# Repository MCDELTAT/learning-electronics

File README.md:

# Learning Electronics
## Author: Aaron Chamberlain

This repository holds simple circuit boards that are great for learning about electronics. Simply navigate to the individual folders for each project. In them, you will find the EAGLE board, schematic, and project files. In some cases there will be two versions, one to be milled on a CNC (I use the Bantam Tools CNC Machine to test these) and another to be manufactured by a service like OSHPARK. Both versions cant be sent to a manufacturer, but the CNC versions are not optimal because I often leave out vias, which are difficult to make on a milled board.

## Projects:
[Transistor Logic][logic]: This circuit is a simple implementation of the 4 basic logic gates, AND, OR, NOR, and NAND.

[logic]: ./transistor_logic/

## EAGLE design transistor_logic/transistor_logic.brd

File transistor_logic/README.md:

# Transistor Logic
This circuit is a simple implementation of the 4 basic logic gates, AND, OR, NOR, and NAND.

At this time, the circuit only has a version designed for a CNC machine. I will consider making a different version for fabrication with good silkscreens.

Bill of Materials (The Stuff You Need to Make This):

I recommend using Digikey or Mouser to find these products, I will try to provide part-numbers for them when possible.

* 1 9V Battery or Power Supply
* 1 8-Pin DIP Switch
* 8 3904 NPN Transistors
* 8 10K 1/2W Resistors
* 4 4.7K 1/2W Resistors
* 4 120R 1/2W Resistors
* 4 5mm LEDs of your choice

Note that it it recommended to change the resistor value of the 120R resistor if you change the LED color. I chose 120R because it's roughly middle of the road and what I needed for 4 green LEDs.

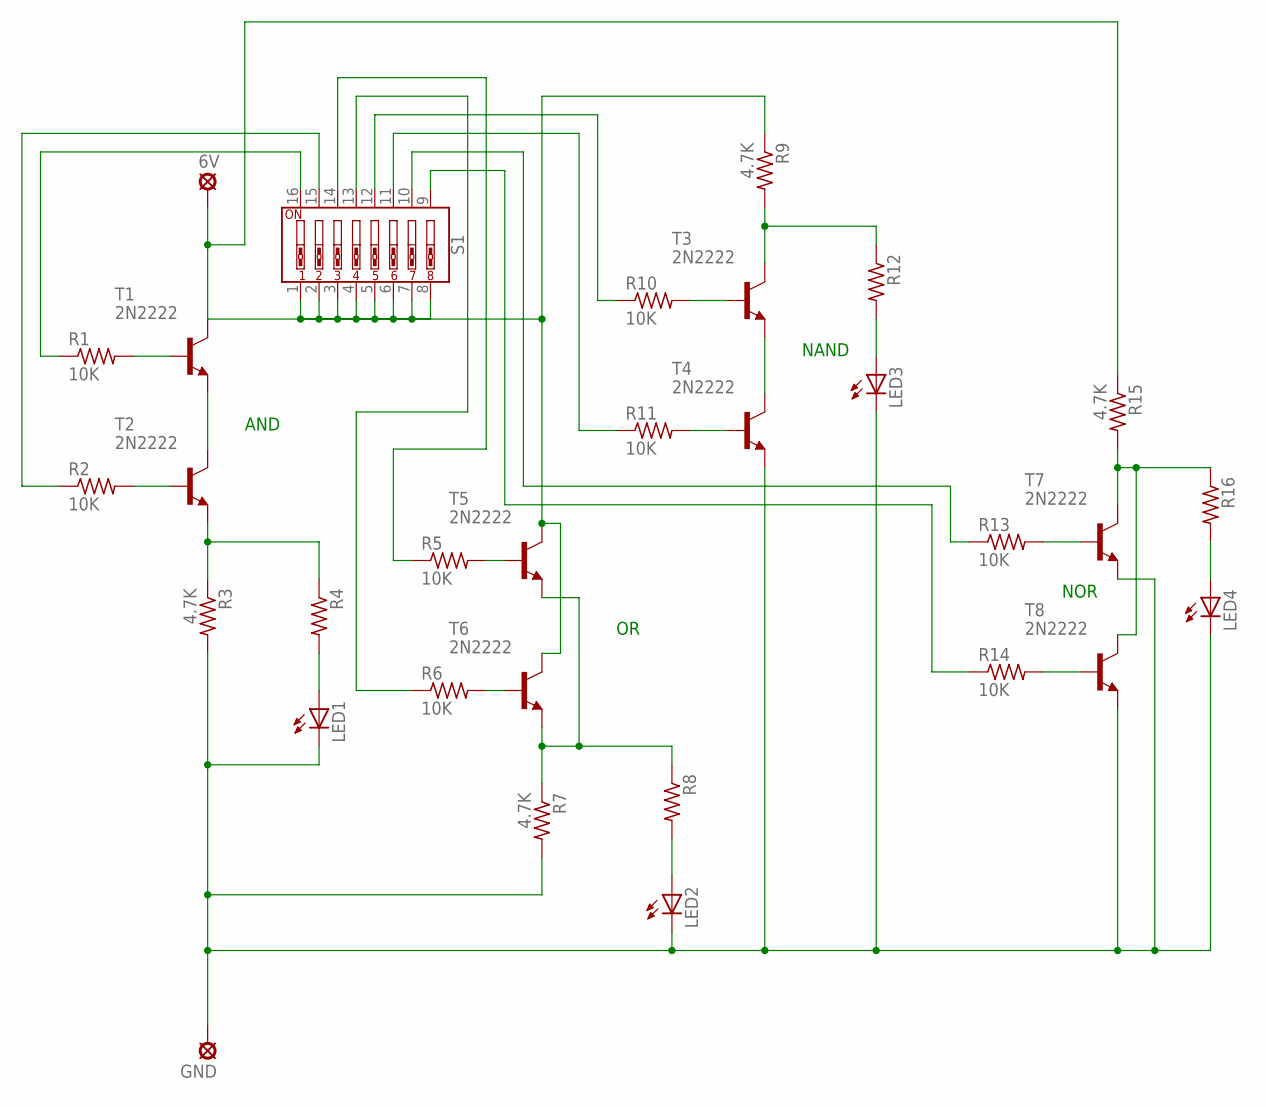
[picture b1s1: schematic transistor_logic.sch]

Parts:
6V: 6V; LSP07
GND: GND; LSP07
LED1, LED2, LED3, LED4: LED5MM
R1, R2, R5, R6, R10, R11, R13, R14: 10K; 0207/9
R3, R7, R9, R15: 4.7K; 0207/9
R4, R8, R12, R16: R-US_0207/9; 0207/9
S1: DIP-08-PTH; DIPSWITCH-08
T1, T2, T3, T4, T5, T6, T7, T8: 2N2222; TO92-EBC-OVAL

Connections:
unnamed: R1.2, T1.B
unnamed: T1.E, T2.C
unnamed: R2.2, T2.B
unnamed: R3.1, R4.1, T2.E
unnamed: LED1.A, R4.2
unnamed: 6V.P$1, R9.1, R15.1, S1.1, S1.2, S1.3, S1.4, S1.5, S1.6, S1.7, S1.8, T1.C, T5.C, T6.C
unnamed: GND.P$1, LED1.K (C), LED2.K (C), LED3.K (C), LED4.K (C), R3.2, R7.2, T4.E, T7.E, T8.E
unnamed: R1.1, S1.16
unnamed: R2.1, S1.15
unnamed: R5.2, T5.B
unnamed: R6.2, T6.B
unnamed: R7.1, R8.1, T5.E, T6.E
unnamed: LED2.A, R8.2
unnamed: R5.1, S1.14
unnamed: R6.1, S1.13
unnamed: R9.2, R12.1, T3.C
unnamed: T3.E, T4.C
unnamed: R10.2, T3.B
unnamed: R11.2, T4.B
unnamed: LED3.A, R12.2
unnamed: R10.1, S1.12
unnamed: R11.1, S1.11
unnamed: R13.2, T7.B
unnamed: R14.2, T8.B
unnamed: R15.2, R16.1, T7.C, T8.C
unnamed: LED4.A, R16.2
unnamed: R13.1, S1.10
unnamed: R14.1, S1.9

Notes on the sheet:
AND
NAND
NOR

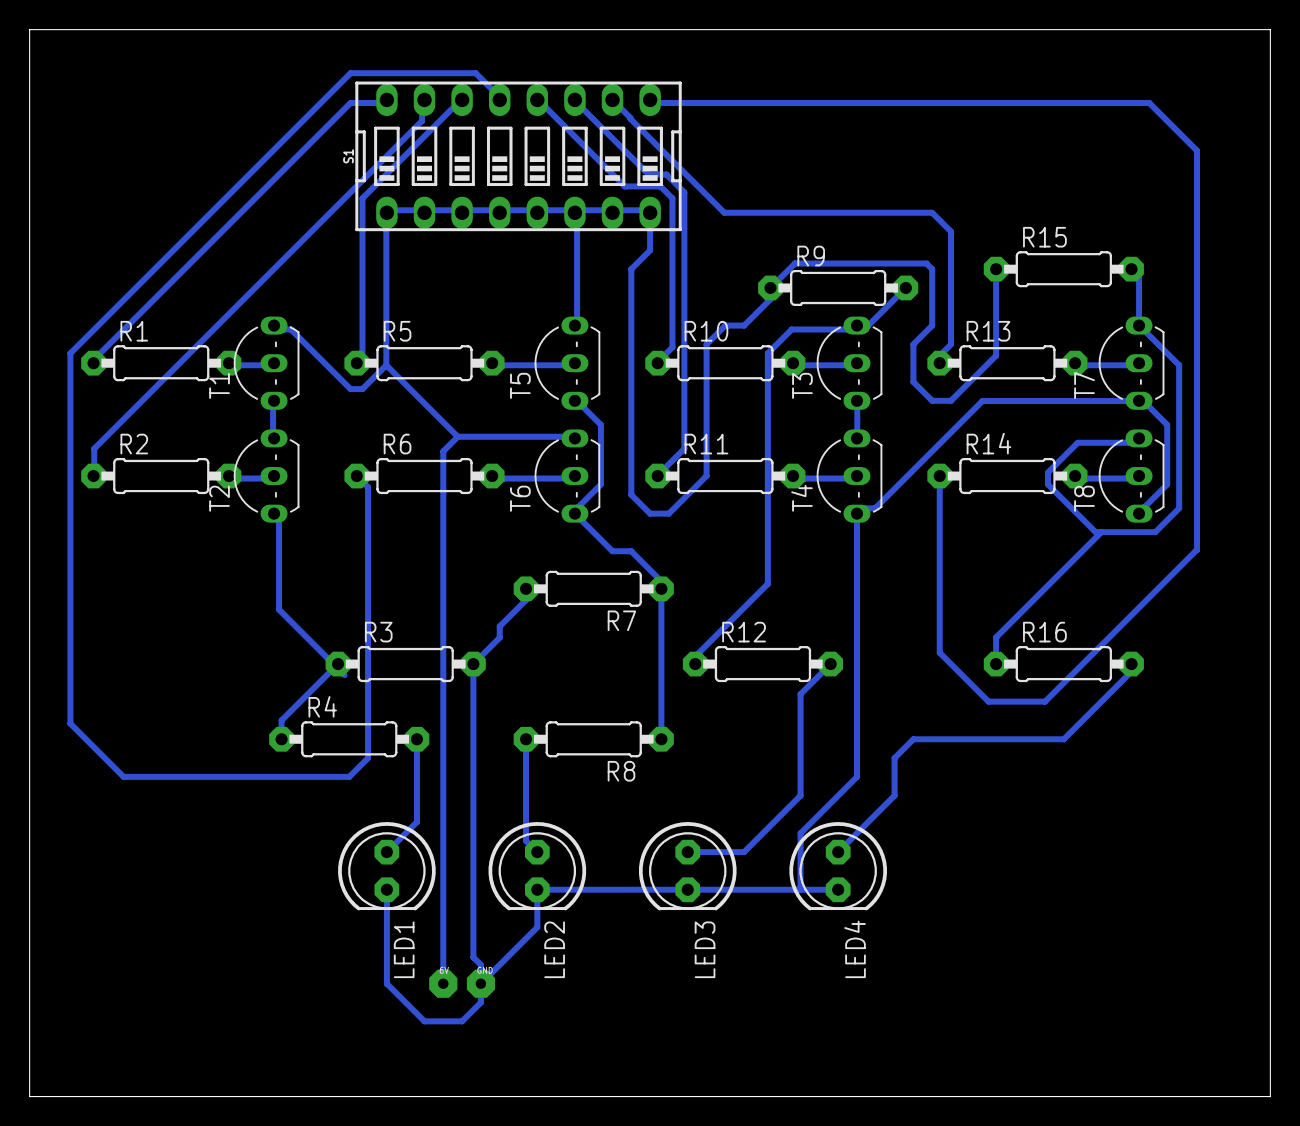
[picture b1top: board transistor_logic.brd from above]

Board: 2 copper layers, 83.8 x 72.1 mm, 31 parts (0 on the bottom side), 28 nets.

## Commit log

2018-03-29 Updated to Include My Transistor Logic Board
    This board is the v1 that functions as expected, but may get revised for clarity and to use thicker traces for better milling repeatability.
2018-03-29 Updated Transistor Logic README for Readability

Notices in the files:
parts and their libraries:
SparkFun-Switches: Licensing: Creative Commons ShareAlike 4.0 International - https://creativecommons.org/licenses/by-sa/4.0
